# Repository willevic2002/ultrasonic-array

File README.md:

# ultrasonic-array

Egenbyggd 3D-ultraljudssensor för min robot: en 40 kHz-sändare och en array med
16 digitala MEMS-mikrofoner (PDM). Riktning och avstånd till hinder bestäms med
chirp, matchat filter och beamforming. Idén liknar Sonairs ADAR: ett platt kort
som ser i 3D (riktning + avstånd) inom en kupol framför sig. Se [docs/notes.md](docs/notes.md).

> **Lärprojekt.** Det här är ingen certifierad säkerhetsfunktion och ska inte
> användas som enda skydd mot kollisioner.

*Skiss: enheten framifrån (skalenlig), från sidan med synfältet, och fyra enheter
runt en robot. Genereras av `tools/draw_sketch.py` från `hardware/mic_placement.csv`.*

## Arkitektur

```
 40 kHz-givare ◄── drivare (TC4427A, 10-12 V) ◄── TX ─┐
                                                      │
 16 x SPH0641LU4H-1 ── 8 x DATA + 1 x CLK ──► FPGA (Boolean Board, Spartan-7)
   (Vogel-spiral, 84x84 mm)                    │  klockgenerering, PDM-inläsning,
                                               │  CIC-decimering
                                               ▼
                                         Raspberry Pi
                                           beamforming, loggning, (ROS 2)
```

- **Mikrofoner:** Knowles SPH0641LU4H-1, PDM med ultraljudsläge. Två mikrofoner delar
  en DATA-linje (SELECT väljer klockflank). 16 mikrofoner blir 8 DATA-linjer + 1 delad CLK.
- **Sändare:** Same Sky CUSA-T75-18-2400-TH (Ø12,5 mm, ersätter Murata MA40S4S som är not for new designs) och drivare
  med 10-12 V. Sitter i mitten av arrayen.
- **FPGA:** Real Digital Boolean Board (XC7S50, `xc7s50csga324-1`), VHDL i Vivado.
  Spartan-7 har ingen DFSDM-hårdvara, så PDM läses och decimeras i logiken.
- **Raspberry Pi:** SPI-master. Startar en ping, läser inspelningen (16 kanaler x 2048 sampel)
  och kör matchat filter och beamforming. Se [docs/pipeline.md](docs/pipeline.md).

## Status

Ärligt läge, oktober 2026:

| Del | Status |
|---|---|
| Steg 1: färdig HC-SR04-modul avläst med STM32 | ✅ Fungerar (utanför detta repo) |
| PDM-mikrofonerna (SPH0641LU4H-1) | ❌ Inte testade i hårdvara än |
| Steg 3: eget kort, 16 mikrofoner | 🚧 Utkast. Placering klar och reproducerbar från skript, designkontroller (DRC + egna) går igenom, footprints är platshållare, inga ledningar, inget jordplan, ingen sändare |
| `fpga/`: hela kedjan (klocka, 16 kanaler, CIC, chirp, inspelning, SPI till Pi) | 🧪 Simulerad i xsim, bitexakt mot Python-modellen, syntetiserad med timing uppfylld. **Otestad i hårdvara** |
| `fpga/constraints/`: pinnar | 🧪 Valda på PMOD JA/JB/JC, utlästa ur schemat, ska verifieras |
| `software/`: delay-and-sum offline | 🧪 Testad på syntetisk data, **aldrig körd på riktig mätdata** |
| `software/`: SPI-klient för Pi:n, matchat filter, Python-modell av PDM/CIC | 🧪 Testad mot en falsk FPGA och i simuleringen av hela kedjan |
| `software/`: ROS 2 | ❌ Inte påbörjat |

Alla tekniska fakta om mikrofonen och Boolean Board (pinnar, klockintervall,
tidsparametrar) ska verifieras mot datablad. Se [docs/datasheets.md](docs/datasheets.md).

## Repo-struktur

```
hardware/    KiCad-kort, footprints och genereringsskript (CERN-OHL-P)
fpga/        VHDL-källor, testbänkar, constraints
software/    Python: inläsning av loggdata och beamforming
docs/        datablad-länkar, anteckningar, bilder
tools/       hjälpskript
```

## Bygga och köra

### FPGA-simulering

Kräver Vivado 2026.1 (xsim). Se [fpga/README.md](fpga/README.md).

```bash
fpga/sim/run_xsim.sh
```

### Python

```bash
cd software
python -m venv .venv && source .venv/bin/activate
pip install -r requirements.txt
pytest
python -m beamforming data.npz --mics ../hardware/mic_placement.csv --range 1.0
python -m sonar --fake --out /tmp/x.npz --mics ../hardware/mic_placement.csv  # avstånd + riktning
```

### Kortet

Öppna `hardware/kicad/mic_array.kicad_pcb` i KiCad 10. Designkontroller (KiCads DRC
plus egna kontroller):

```bash
pytest hardware/tests
```

Se [hardware/README.md](hardware/README.md).

## TODO

Öppna punkter finns som [GitHub Issues](https://github.com/willevic2002/ultrasonic-array/issues) (översikt i [TODO.md](TODO.md)). Ändringar loggas i [CHANGELOG.md](CHANGELOG.md).

## Licens

- Kod (`fpga/`, `software/`, `tools/`): [MIT](LICENSE)
- Hårdvara (`hardware/`): [CERN-OHL-P-2.0](hardware/LICENSE)

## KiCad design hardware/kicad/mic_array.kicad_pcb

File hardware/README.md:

# hardware

Licens: CERN-OHL-P-2.0 (se [LICENSE](LICENSE)).

## Var filerna ska ligga

| Fil | Plats |
|---|---|
| `mic_array.kicad_pcb` (16 mikrofoner), `mic_test.kicad_pcb` (testkort, 2 mikrofoner) | `kicad/` |
| `place_mics.py`, `make_kicad_pcb.py` | `scripts/` |
| `mic_placement.csv` | här (`hardware/`) |
| Riktiga footprints (`.kicad_mod` / `.pretty`) | `footprints/` |

## Generera kortet

```bash
python3 hardware/scripts/place_mics.py     # -> hardware/mic_placement.csv
python3 hardware/scripts/make_kicad_pcb.py # -> hardware/kicad/mic_array.kicad_pcb + mic_test.kicad_pcb
```

Skripten hittar sina filer relativt sig själva och kan köras från vilken mapp som helst.
`place_mics.py` placerar mikrofonerna i en Vogel-spiral: r = 8,5·√(i+1,5) mm,
vinkel = i·137,508°. Min. avstånd 13,95 mm, innersta mikrofonen 10,4 mm från mitten.
Första utkastet hade √(i+0,5), men då hamnade U1 under sändaren.

Mikrofonerna använder KiCads footprint `Sensor_Audio:Knowles_LGA-5_3.5x2.65mm`
(efter Knowles datablad rev B), med 0,5 mm hål under ljudporten och jordring runt det.
Porten sitter 0,77 mm från kapselns mitt. Footprinten placeras så att **porten**
hamnar på positionen i `mic_placement.csv`, så csv:n anger de akustiska positionerna.

`make_kicad_pcb.py` lägger också in courtyards och en keepout-zon (`TX_KEEPOUT`,
radie 7,25 mm) i mitten där sändaren ska sitta. Radien förutsätter Same Sky
CUSA-T75-18-2400-TH (Ø12,5 mm) och ska ändras om en annan sändare väljs (#4).

## Testa designen

```bash
pytest hardware/tests
```

Kör KiCads DRC via `kicad-cli` och kontrollerar det DRC inte kan veta utan schema:
nät per mikrofon, att varje DATA-par har en GND- och en VDD-SEL, avkoppling,
minsta avstånd, att allt ryms på kortet och att mitten är fri för sändaren.
Tillåtna DRC-avvikelser i utkastet: oanslutna nät (inga ledningar än) och
platshållar-footprints som saknas i bibliotek. När det finns ett schema kan
parity och ERC ta över en del av kontrollerna.

Obs: `make_kicad_pcb.py` skriver över `mic_array.kicad_pcb`. Så fort du börjar
dra ledningar i KiCad ska du sluta köra skriptet (eller ändra det att skriva till en annan fil).

## Läge

`mic_array.kicad_pcb` är ett **utkast** genererat av `make_kicad_pcb.py`:

- 16 mikrofoner i Vogel-spiral, min. avstånd 13,9 mm, kort 84 x 84 mm
- Courtyards och keepout för sändaren i mitten
- Riktig mikrofon-footprint med porthål
- Inga ledningar, inget jordplan, ingen sändare/drivare

## Testkort (`mic_test.kicad_pcb`)

30 x 22 mm med 2 mikrofoner på samma DATA-linje (U1 SEL=GND, U2 SEL=VDD), 14 mm isär,
en 100 nF per mikrofon och en 1x6 stiftlist med 2,54 mm delning enligt Digilents
Pmod-standard: 1 CLK, 2 DATA, 5 GND, 6 3V3. Passar i breadboard och i Boolean-kortets
Pmod-kontakt (verifiera pinout och 3,3 V). Syftet är att testa footprint, porthål,
SEL-parning och VHDL-inläsningen innan 16-mikrofonskortet beställs.

Öppna punkter finns i [../TODO.md](../TODO.md).

## Att komma ihåg (verifiera mot datablad)

- SPH0641LU4H-1 pinnar (enligt mina anteckningar): 1 DATA, 2 SELECT, 3 GND, 4 CLOCK, 5 VDD.
  VDD 1,62-3,6 V.
- Akustisk port på undersidan: hål i kortet under varje mikrofon.
- 0,1 µF C0G/NP0 vid varje VDD-pinne.
- Tvätta inte kortet efter lödning.

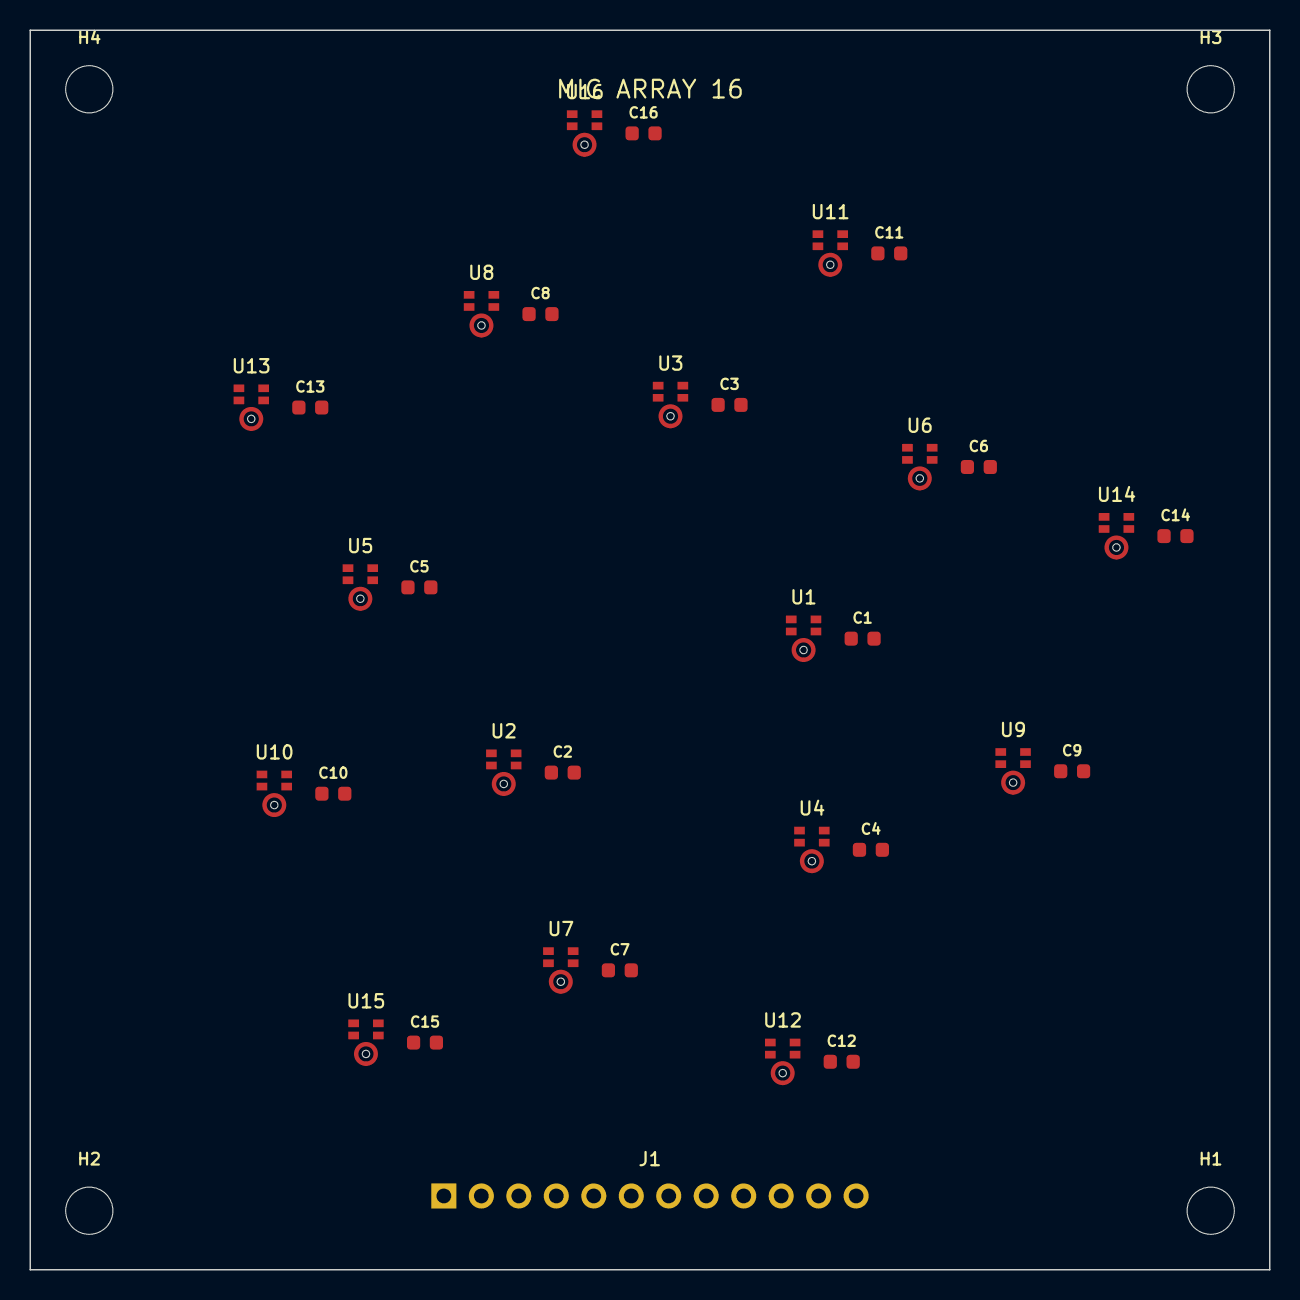
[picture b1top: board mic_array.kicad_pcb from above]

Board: 2 copper layers, 84.0 x 84.0 mm, 37 parts (0 on the bottom side), 11 nets, no tracks yet.

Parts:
C1, C2, C3, C4, C5, C6, C7, C8, C9, C10, C11, C12, C13, C14, C15, C16: 100nF C0G; C_0603_1608Metric
H1, H2, H3, H4: M3; MountingHole_3.2mm_M3
J1: CLK D1-D8 3V3 GND GND; PinHeader_1x12_P2.54mm_Vertical
U1, U2, U3, U4, U5, U6, U7, U8, U9, U10, U11, U12, U13, U14, U15, U16: SPH0641LU4H-1; Knowles_LGA-5_3.5x2.65mm

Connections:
+3V3: C1.1, C2.1, C3.1, C4.1, C5.1, C6.1, C7.1, C8.1, C9.1, C10.1, C11.1, C12.1, C13.1, C14.1, C15.1, C16.1, J1.10, U1.5, U2.5, U3.5, U4.2, U4.5, U5.5, U6.5, U7.2, U7.5, U8.2, U8.5, U9.5, U10.5, U11.5, U12.2, U12.5, U13.2, U13.5, U14.2, U14.5, U15.2, U15.5, U16.2, U16.5
CLK: J1.1, U1.4, U2.4, U3.4, U4.4, U5.4, U6.4, U7.4, U8.4, U9.4, U10.4, U11.4, U12.4, U13.4, U14.4, U15.4, U16.4
DATA1: J1.2, U1.1, U4.1
DATA2: J1.3, U2.1, U7.1
DATA3: J1.4, U3.1, U8.1
DATA4: J1.5, U5.1, U13.1
DATA5: J1.6, U6.1, U14.1
DATA6: J1.7, U9.1, U12.1
DATA7: J1.8, U10.1, U15.1
DATA8: J1.9, U11.1, U16.1
GND: C1.2, C2.2, C3.2, C4.2, C5.2, C6.2, C7.2, C8.2, C9.2, C10.2, C11.2, C12.2, C13.2, C14.2, C15.2, C16.2, J1.11, J1.12, U1.2, U1.3, U2.2, U2.3, U3.2, U3.3, U4.3, U5.2, U5.3, U6.2, U6.3, U7.3, U8.3, U9.2, U9.3, U10.2, U10.3, U11.2, U11.3, U12.3, U13.3, U14.3, U15.3, U16.3

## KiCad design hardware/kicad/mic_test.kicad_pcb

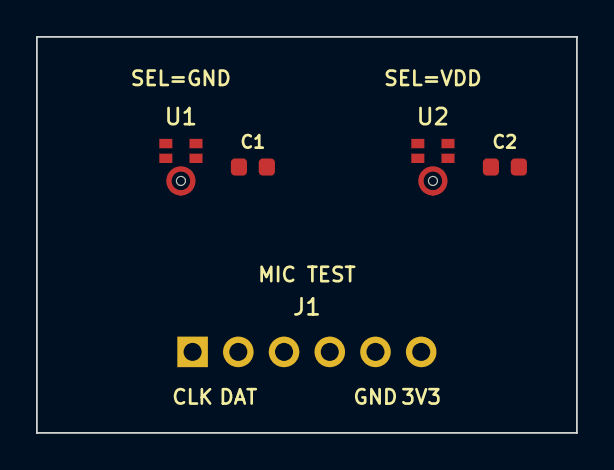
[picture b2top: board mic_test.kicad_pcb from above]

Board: 2 copper layers, 30.0 x 22.0 mm, 5 parts (0 on the bottom side), 4 nets, no tracks yet.

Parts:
C1, C2: 100nF C0G; C_0603_1608Metric
J1: PMOD 1 CLK 2 DATA 5 GND 6 3V3; PinHeader_1x06_P2.54mm_Vertical
U1, U2: SPH0641LU4H-1; Knowles_LGA-5_3.5x2.65mm

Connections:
+3V3: C1.1, C2.1, J1.6, U1.5, U2.2, U2.5
CLK: J1.1, U1.4, U2.4
DATA1: J1.2, U1.1, U2.1
GND: C1.2, C2.2, J1.5, U1.2, U1.3, U2.3
